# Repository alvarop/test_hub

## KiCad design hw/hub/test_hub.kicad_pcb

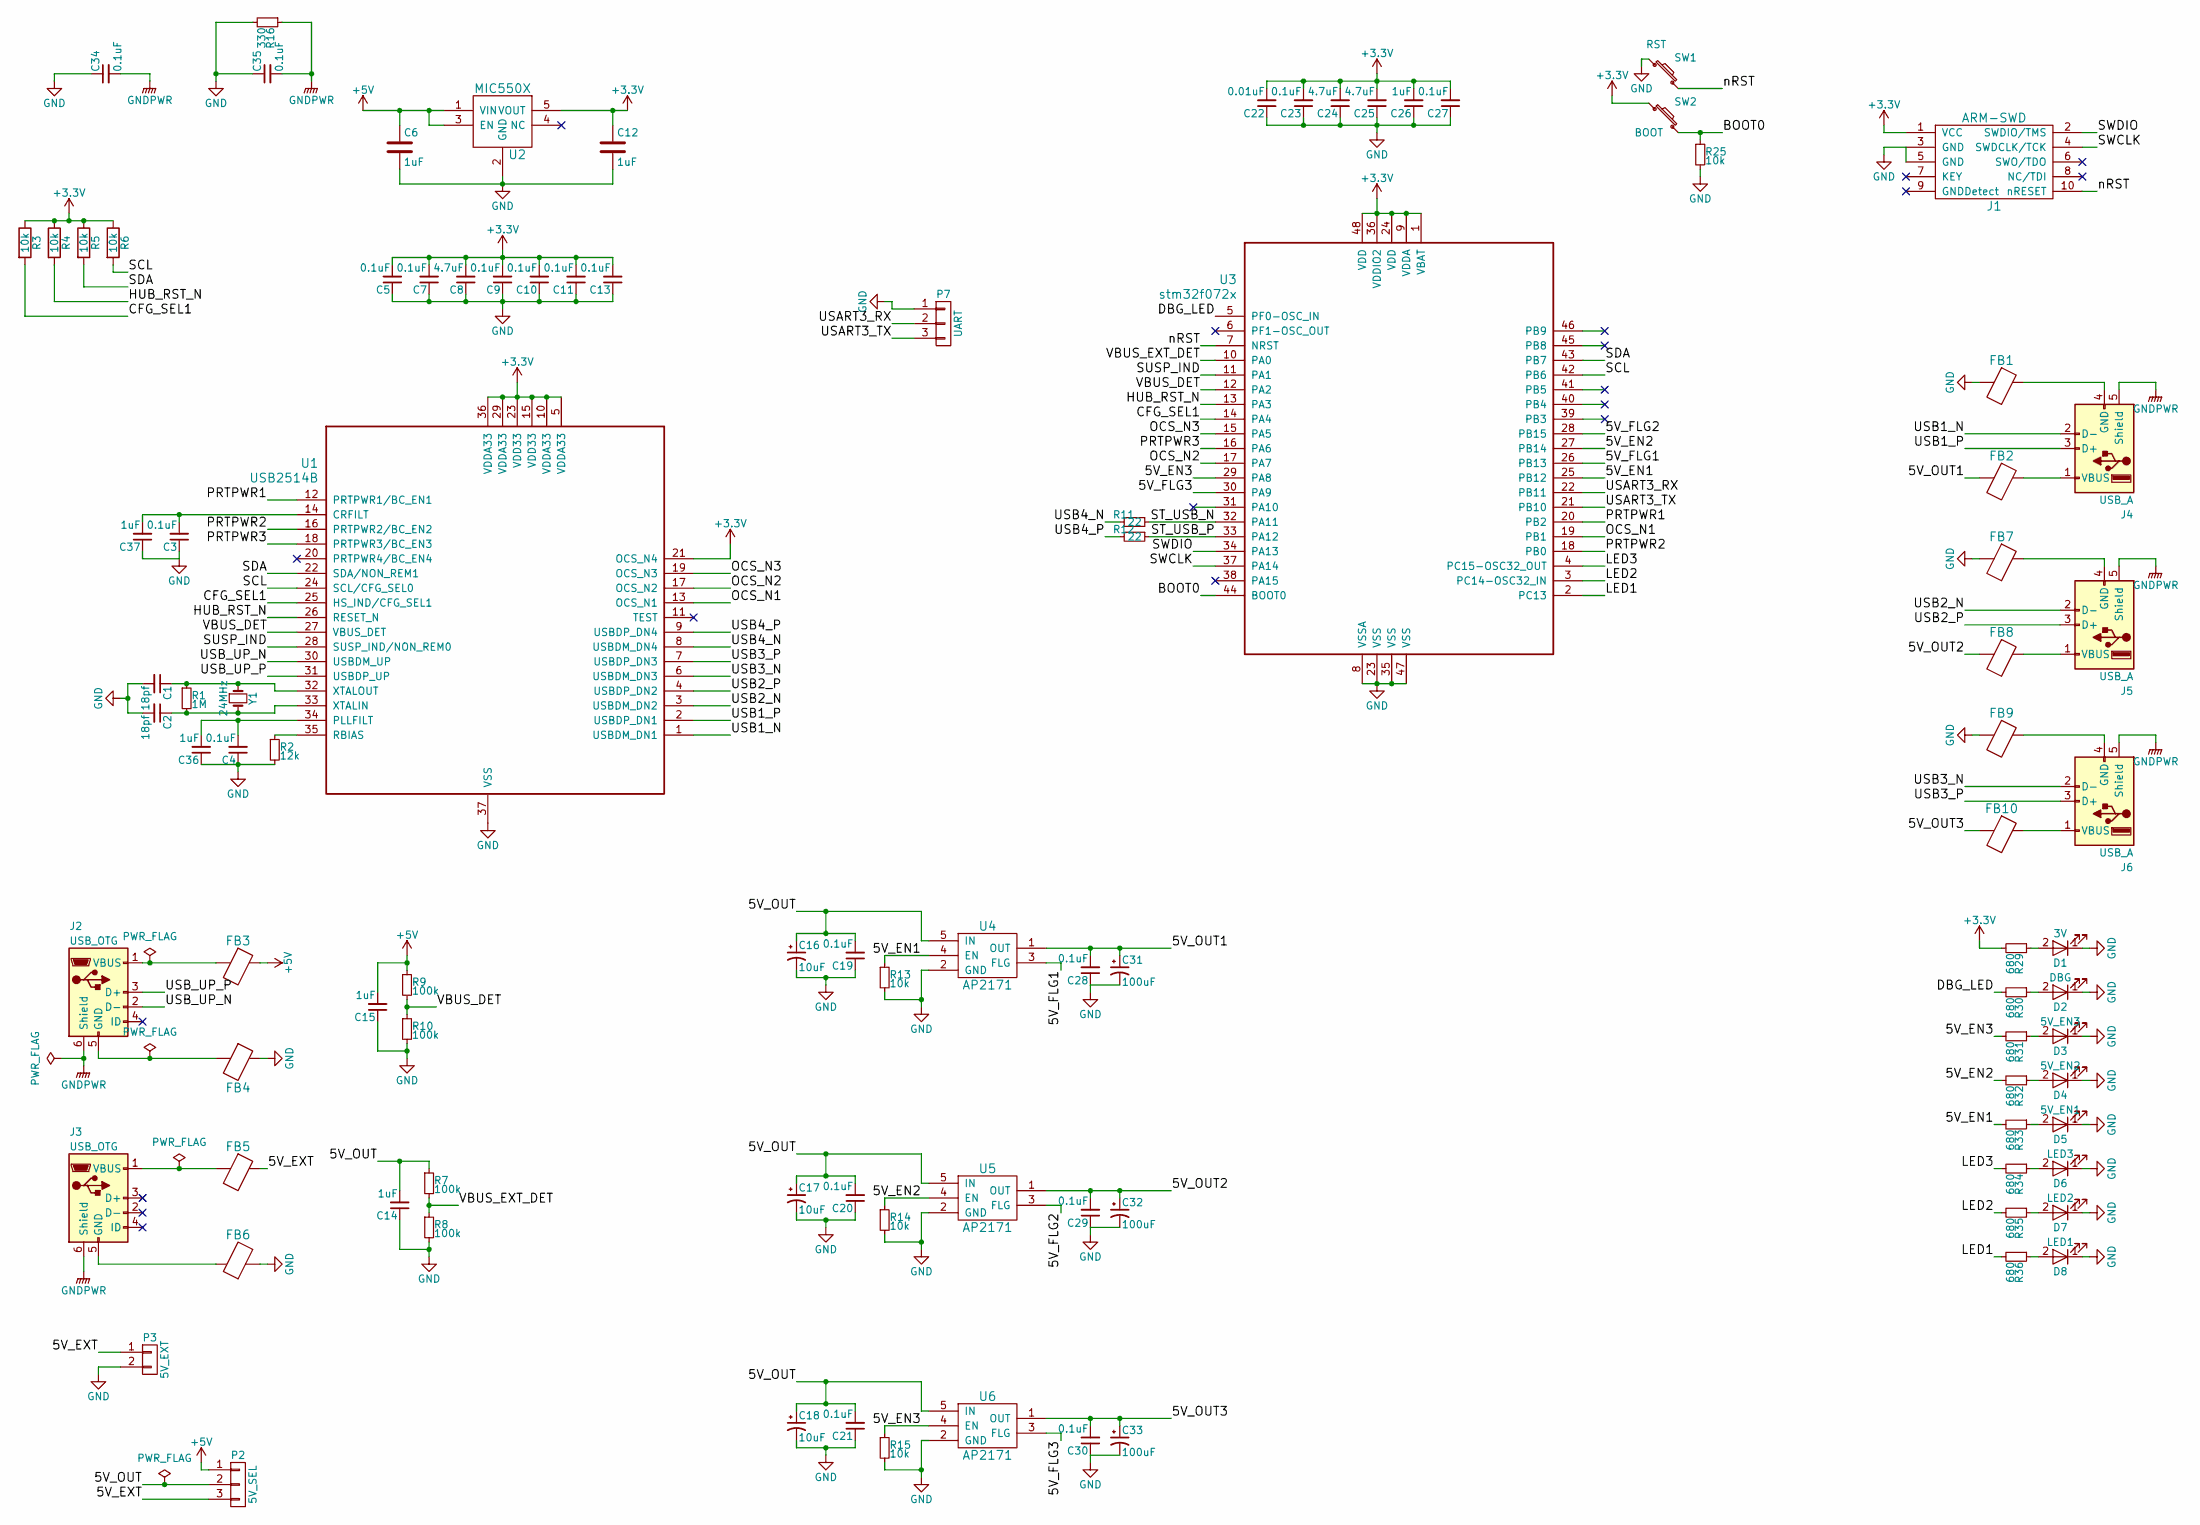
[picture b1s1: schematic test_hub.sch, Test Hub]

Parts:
C1, C2: 18pf; C_0603; MPN CL10C180JB8NNNC
C3, C4, C5, C7, C9, C10, C11, C13, C19, C20, C21, C23, C27, C28, C29, C30, C34, C35: 0.1uF; C_0603; MPN CC0603ZRY5V9BB104
C6, C12, C14, C15, C26, C36, C37: 1uF; C_0603; MPN GRM188R61C105KA93D
C8, C24, C25: 4.7uF; C_0603; MPN CL10B475KQ8NQNC
C16, C17, C18: 10uF; c_elec_4x5.3; MPN UWX1C100MCL1GB
C22: 0.01uF; C_0603; MPN CL21B103KBANNNC
C31, C32, C33: 100uF; c_elec_6.3x5.7; MPN UWR1A101MCL1GB
D1: 3V; LED_0805; MPN LG R971-KN-1
D2: DBG; LED_0805; MPN LG R971-KN-1
D3: 5V_EN3; LED_0805; MPN LG R971-KN-1
D4: 5V_EN2; LED_0805; MPN LG R971-KN-1
D5: 5V_EN1; LED_0805; MPN LG R971-KN-1
D6: LED3; LED_0805; MPN LG R971-KN-1
D7: LED2; LED_0805; MPN LG R971-KN-1
D8: LED1; LED_0805; MPN LG R971-KN-1
FB1, FB2, FB3, FB4, FB5, FB6, FB7, FB8, FB9, FB10: Ferrite_Bead; R_0603; MPN CIS10P221NC
J1: ARM-SWD; ARM_SWD_SMD; MPN 20021121-00010C4LF
J2, J3: USB_OTG; USB_MICRO_B; MPN 629105150521
J4, J5, J6: USB_A; 292303-1; MPN 292303-1
P2: 5V_SEL; Pin_Header_Straight_1x03
P3: 5V_EXT; Pin_Header_Straight_1x02
P7: UART; Pin_Header_Straight_1x03
R1: 1M; R_0603; MPN ERJ-3GEYJ105V
R2: 12k; R_0603; MPN ERJ-3EKF1202V
R3, R4, R5, R6, R13, R14, R15, R25: 10k; R_0603; MPN RC0603FR-0710KL
R7, R8, R9, R10: 100k; R_0603; MPN ERJ-3GEYJ104V
R11, R12: 22; R_0603; MPN RC0603FR-0722RL
R16: 330; R_0603; MPN RC0603JR-07330RL
R29, R30, R31, R32, R33, R34, R35, R36: 680; R_0603; MPN RC0603JR-07680RL
SW1: RST; PTS645SM43SMTR92; MPN PTS645SM43SMTR92
SW2: BOOT; PTS645SM43SMTR92; MPN PTS645SM43SMTR92
U1: USB2514B; SQFN36; MPN USB2514B/M2
U2: MIC550X; SOT-23(M5); MPN MIC5504-3.3YM5-TR
U3: stm32f072x; LQFP48; MPN STM32F072RBT6
U4, U5, U6: AP2171; SOT-25; MPN AP2171WG-7
Y1: 24MHz; HCM49; MPN HCM4924000000ABJT

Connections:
+3V3: C5.2, C7.2, C8.2, C9.2, C10.2, C11.2, C12.1, C13.2, C22.2, C23.2, C24.2, C25.2, C26.2, C27.2, J1.1 (VCC), R3.1, R4.1, R5.1, R6.1, R29.2, SW2.1, U1.5 (VDDA33), U1.10 (VDDA33), U1.15 (VDD33), U1.21 (OCS_N4), U1.23 (VDD33), U1.29 (VDDA33), U1.36 (VDDA33), U2.5 (VOUT), U3.1 (VBAT), U3.9 (VDDA), U3.24 (VDD), U3.36 (VDDIO2), U3.48 (VDD)
+5V: C6.1, C15.2, FB3.2, P2.1, R9.1, U2.1 (VIN), U2.3 (EN)
/5V_EN1: R13.1, R33.2, U3.25 (PB12), U4.4 (EN)
/5V_EN2: R14.1, R32.2, U3.27 (PB14), U5.4 (EN)
/5V_EN3: R15.1, R31.2, U3.29 (PA8), U6.4 (EN)
/5V_EXT: FB5.2, P2.3, P3.1
/5V_FLG1: U3.26 (PB13), U4.3 (FLG)
/5V_FLG2: U3.28 (PB15), U5.3 (FLG)
/5V_FLG3: U3.30 (PA9), U6.3 (FLG)
/5V_OUT: C14.2, C16.1, C17.1, C18.1, C19.2, C20.2, C21.2, P2.2, R7.1, U4.5 (IN), U5.5 (IN), U6.5 (IN)
/5V_OUT1: C28.2, C31.1, FB2.1, U4.1 (OUT)
/5V_OUT2: C29.2, C32.1, FB8.1, U5.1 (OUT)
/5V_OUT3: C30.2, C33.1, FB10.1, U6.1 (OUT)
/BOOT0: R25.1, SW2.2, U3.44 (BOOT0)
/CFG_SEL1: R3.2, U1.25 (HS_IND/CFG_SEL1), U3.14 (PA4)
/DBG_LED: R30.2, U3.5 (PF0-OSC_IN)
/HUB_RST_N: R4.2, U1.26 (RESET_N), U3.13 (PA3)
/LED1: R36.2, U3.2 (PC13)
/LED2: R35.2, U3.3 (PC14-OSC32_IN)
/LED3: R34.2, U3.4 (PC15-OSC32_OUT)
/OCS_N1: U1.13 (OCS_N1), U3.19 (PB1)
/OCS_N2: U1.17 (OCS_N2), U3.17 (PA7)
/OCS_N3: U1.19 (OCS_N3), U3.15 (PA5)
/PRTPWR1: U1.12 (PRTPWR1/BC_EN1), U3.20 (PB2)
/PRTPWR2: U1.16 (PRTPWR2/BC_EN2), U3.18 (PB0)
/PRTPWR3: U1.18 (PRTPWR3/BC_EN3), U3.16 (PA6)
/SCL: R6.2, U1.24 (SCL/CFG_SEL0), U3.42 (PB6)
/SDA: R5.2, U1.22 (SDA/NON_REM1), U3.43 (PB7)
/ST_USB_N: R11.1, U3.32 (PA11)
/ST_USB_P: R12.1, U3.33 (PA12)
/SUSP_IND: U1.28 (SUSP_IND/NON_REM0), U3.11 (PA1)
/SWCLK: J1.4 (SWDCLK/TCK), U3.37 (PA14)
/SWDIO: J1.2 (SWDIO/TMS), U3.34 (PA13)
/USART3_RX: P7.2, U3.22 (PB11)
/USART3_TX: P7.3, U3.21 (PB10)
/USB1_N: J4.2 (D-), U1.1 (USBDM_DN1)
/USB1_P: J4.3 (D+), U1.2 (USBDP_DN1)
/USB2_N: J5.2 (D-), U1.3 (USBDM_DN2)
/USB2_P: J5.3 (D+), U1.4 (USBDP_DN2)
/USB3_N: J6.2 (D-), U1.6 (USBDM_DN3)
/USB3_P: J6.3 (D+), U1.7 (USBDP_DN3)
/USB4_N: R11.2, U1.8 (USBDM_DN4)
/USB4_P: R12.2, U1.9 (USBDP_DN4)
/USB_UP_N: J2.2 (D-), U1.30 (USBDM_UP)
/USB_UP_P: J2.3 (D+), U1.31 (USBDP_UP)
/VBUS_DET: R9.2, R10.1, U1.27 (VBUS_DET), U3.12 (PA2)
/VBUS_EXT_DET: R7.2, R8.1, U3.10 (PA0)
/nRST: J1.10 (nRESET), SW1.2, U3.7 (NRST)
GND: C1.2, C2.2, C3.1, C4.1, C5.1, C6.2, C7.1, C8.1, C9.1, C10.1, C11.1, C12.2, C13.1, C14.1, C15.1, C16.2, C17.2, C18.2, C19.1, C20.1, C21.1, C22.1, C23.1, C24.1, C25.1, C26.1, C27.1, C28.1, C29.1, C30.1, C31.2, C32.2, C33.2, C34.1, C35.1, C36.1, C37.1, D1.1 (K), D2.1 (K), D3.1 (K), D4.1 (K), D5.1 (K), D6.1 (K), D7.1 (K), D8.1 (K), FB1.1, FB4.2, FB6.1, FB7.1, FB9.1, J1.3 (GND), J1.5 (GND), P3.2, P7.1, R2.2, R8.2, R10.2, R13.2, R14.2, R15.2, R16.2, R25.2, SW1.1, U1.37 (VSS), U2.2 (GND), U3.8 (VSSA), U3.23 (VSS), U3.35 (VSS), U3.47 (VSS), U4.2 (GND), U5.2 (GND), U6.2 (GND)
GNDPWR: C34.2, C35.2, J2.6 (Shield), J3.6 (Shield), J4.5 (Shield), J5.5 (Shield), J6.5 (Shield), R16.1
unnamed: C1.1, R1.1, U1.32 (XTALOUT), Y1.1
unnamed: C2.1, R1.2, U1.33 (XTALIN), Y1.2
unnamed: C3.2, C37.2, U1.14 (CRFILT)
unnamed: C4.2, C36.2, U1.34 (PLLFILT)
unnamed: D1.2 (A), R29.1
unnamed: D2.2 (A), R30.1
unnamed: D3.2 (A), R31.1
unnamed: D4.2 (A), R32.1
unnamed: D5.2 (A), R33.1
unnamed: D6.2 (A), R34.1
unnamed: D7.2 (A), R35.1
unnamed: D8.2 (A), R36.1
unnamed: FB1.2, J4.4 (GND)
unnamed: FB2.2, J4.1 (VBUS)
unnamed: FB3.1, J2.1 (VBUS)
unnamed: FB4.1, J2.5 (GND)
unnamed: FB5.1, J3.1 (VBUS)
unnamed: FB6.2, J3.5 (GND)
unnamed: FB7.2, J5.4 (GND)
unnamed: FB8.2, J5.1 (VBUS)
unnamed: FB9.2, J6.4 (GND)
unnamed: FB10.2, J6.1 (VBUS)
unnamed: R2.1, U1.35 (RBIAS)

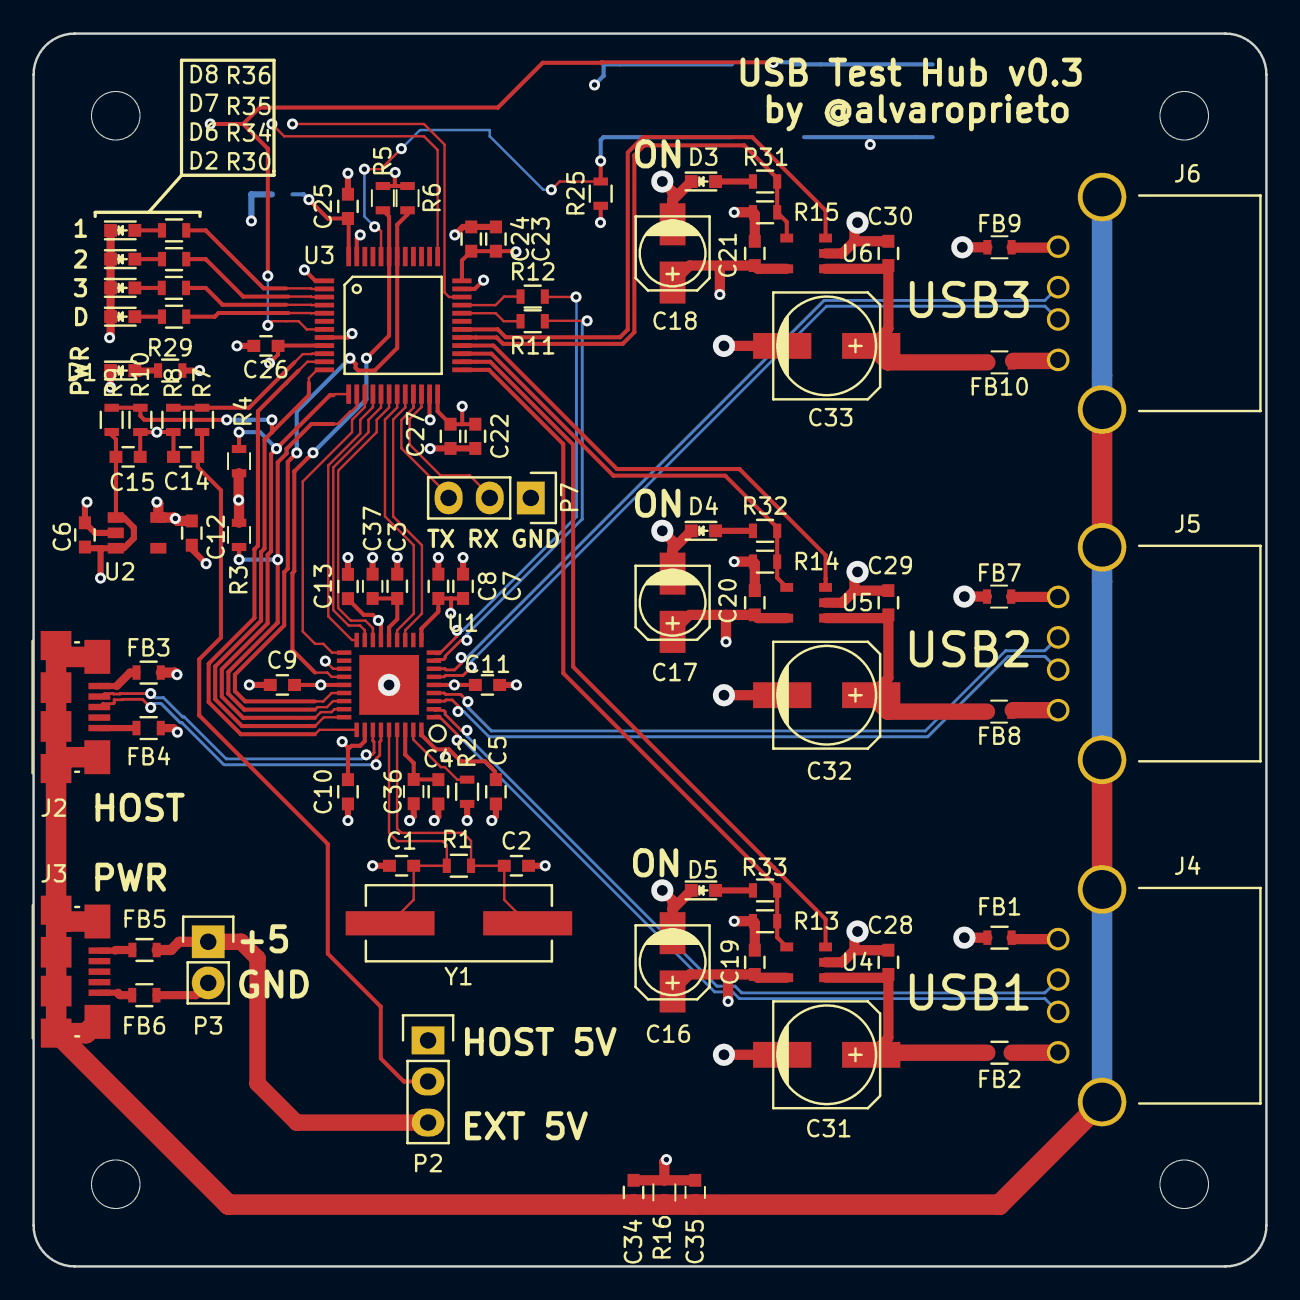
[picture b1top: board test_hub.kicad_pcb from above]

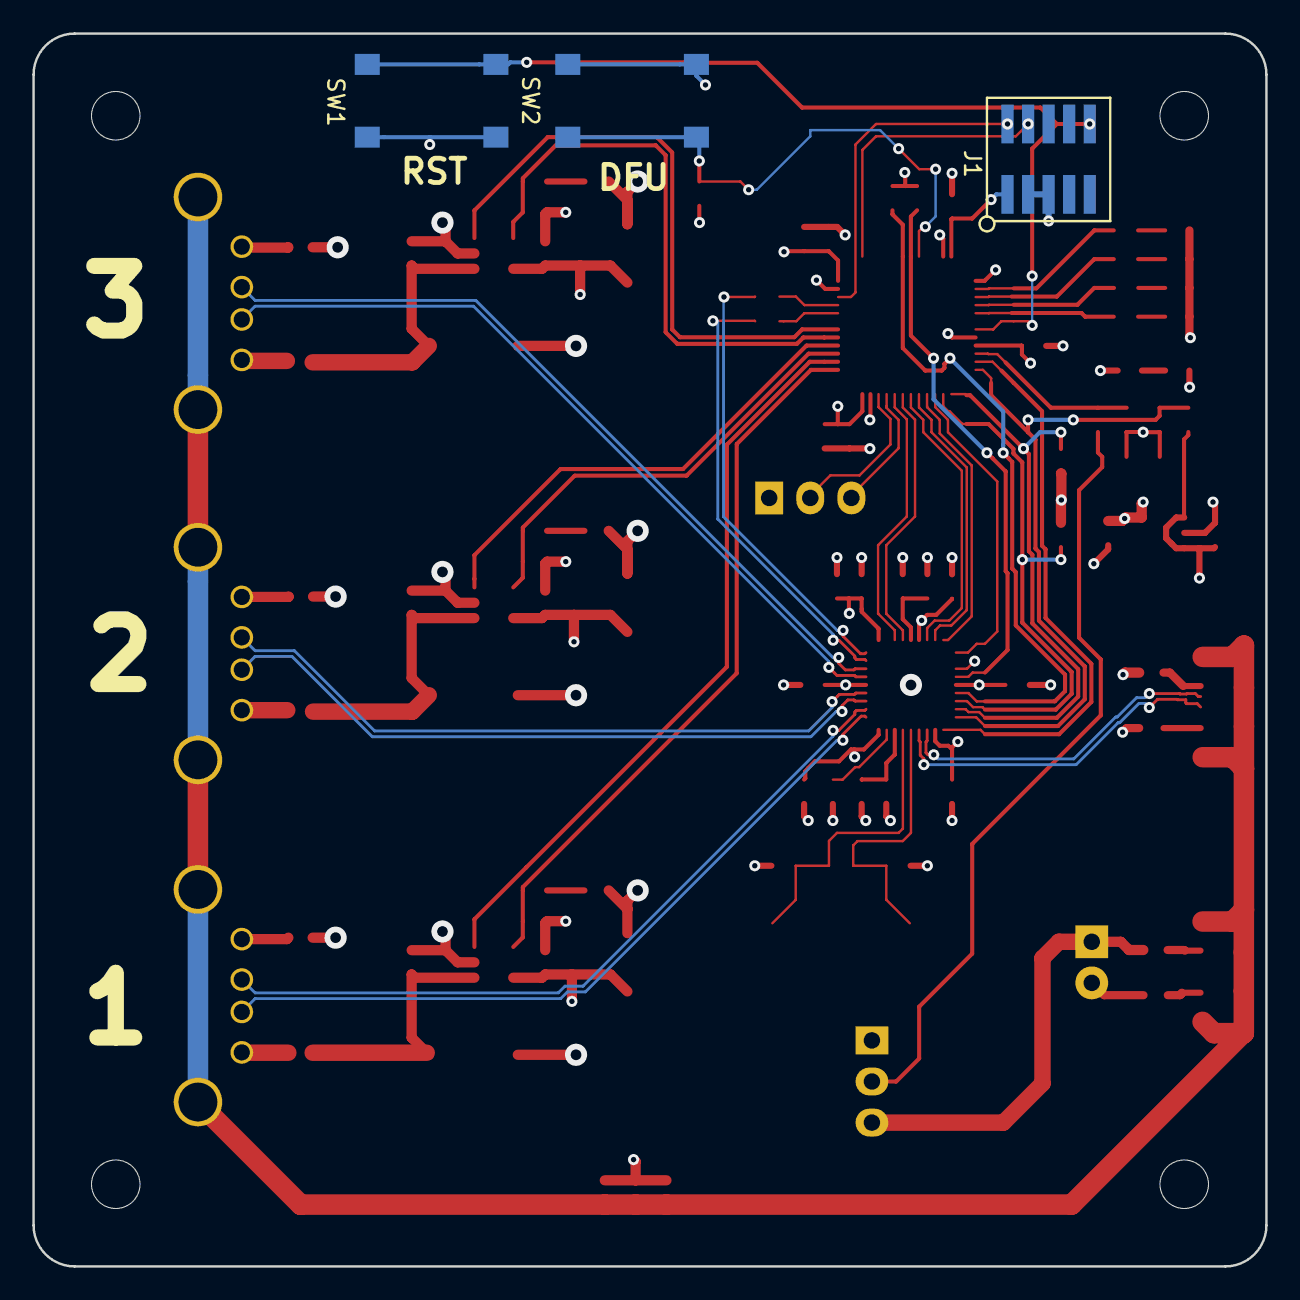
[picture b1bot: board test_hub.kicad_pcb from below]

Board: 4 copper layers, 76.2 x 76.2 mm, 98 parts (3 on the bottom side), 73 nets.

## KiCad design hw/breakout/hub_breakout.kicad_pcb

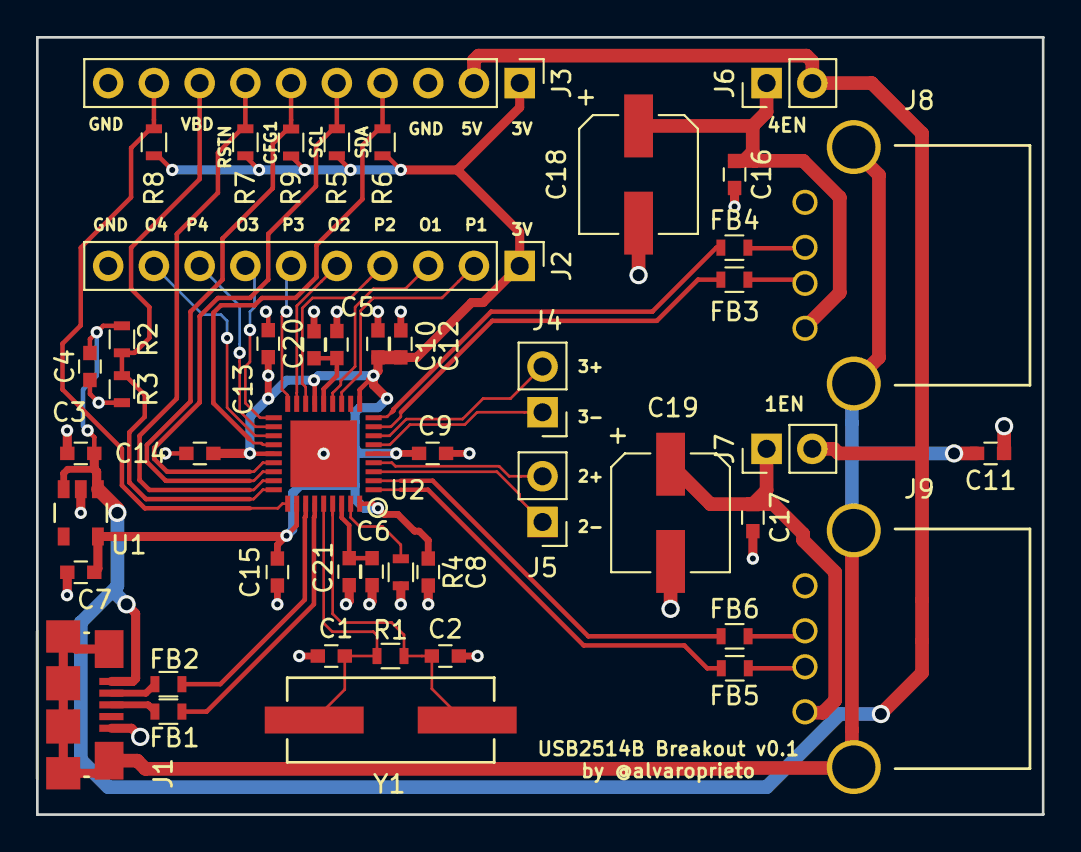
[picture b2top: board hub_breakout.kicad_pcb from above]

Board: 2 copper layers, 55.9 x 43.2 mm, 48 parts (0 on the bottom side), 41 nets.

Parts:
C1, C2: 18pF; C_0603
C3, C4, C7, C20, C21: 1uF; C_0603
C5, C6, C8, C9, C11, C12, C13, C14, C15, C16, C17: 0.1uF; C_0603
C10: 4.7uF; C_0603
C18, C19: 100uF; CP_Elec_6.3x5.7
FB1, FB2, FB3, FB4, FB5, FB6: Ferrite; R_0603
J1: USB_OTG; USB_MICRO_B
J2, J3: CONN_01X10; Pin_Header_Straight_1x10_Pitch2.54mm
J4, J5, J6, J7: CONN_01X02; Pin_Header_Straight_1x02_Pitch2.54mm
J8, J9: USB_A; 292303-1
R1: 1M; R_0603
R2, R3: 100k; R_0603
R4: 12k; R_0603
R5, R6, R7, R8, R9: 10k; R_0603
U1: MIC550X; SOT-23(M5)
U2: USB2514B; SQFN36
Y1: 24MHz; HCM49

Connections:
+3V3: C7.1, C8.1, C9.1, C10.1, C12.1, C13.1, C14.1, C15.1, J2.1, J3.1, R5.1, R6.1, R7.1, R8.1, R9.1, U1.5, U2.5, U2.10, U2.15, U2.23, U2.29, U2.36
+5V: C3.1, C4.1, J1.1, J3.2, J6.2, J7.2, R2.1, U1.1, U1.3
/CFG_SEL1: J3.6, R9.2, U2.25
/OCS_N1: J2.3, U2.13
/OCS_N2: J2.5, U2.17
/OCS_N3: J2.7, U2.19
/OCS_N4: J2.9, U2.21
/PRTPWR1: J2.2, U2.12
/PRTPWR2: J2.4, U2.16
/PRTPWR3: J2.6, U2.18
/PRTPWR4: J2.8, U2.20
/RESET_N: J3.7, R7.2, U2.26
/SCL: J3.5, R5.2, U2.24
/SDA: J3.4, R6.2, U2.22
/SUSP_IND: J3.9, R8.2, U2.28
/USB1_N: FB5.2, U2.1
/USB1_P: FB6.2, U2.2
/USB2_N: J5.1, U2.3
/USB2_P: J5.2, U2.4
/USB3_N: J4.1, U2.6
/USB3_P: J4.2, U2.7
/USB4_N: FB3.2, U2.8
/USB4_P: FB4.2, U2.9
/USB_UP_N: FB2.1, U2.30
/USB_UP_P: FB1.1, U2.31
/VBUS_DET: J3.8, R2.2, R3.1, U2.27
GND: C1.2, C2.2, C3.2, C4.2, C5.2, C6.2, C7.2, C8.2, C9.2, C10.2, C11.1, C12.2, C13.2, C14.2, C15.2, C16.2, C17.2, C18.2, C19.2, C20.2, C21.2, J1.5, J2.10, J3.3, J3.10, J8.4, J9.4, R3.2, R4.2, U1.2, U2.37
GNDPWR: C11.2, J1.6, J8.5, J9.5
unnamed: C1.1, R1.1, U2.32, Y1.1
unnamed: C2.1, R1.2, U2.33, Y1.2
unnamed: C16.1, C18.1, J6.1, J8.1
unnamed: C17.1, C19.1, J7.1, J9.1
unnamed: C5.1, C20.1, U2.14
unnamed: C6.1, C21.1, U2.34
unnamed: FB1.2, J1.3
unnamed: FB2.2, J1.2
unnamed: FB3.1, J8.2
unnamed: FB4.1, J8.3
unnamed: FB5.1, J9.2
unnamed: FB6.1, J9.3
unnamed: R4.1, U2.35

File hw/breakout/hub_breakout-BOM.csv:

Title,
Revision,
Date,
Generated,Mon 27 Mar 2017 06:29:56 PM PDT
Company,
Comment 1,
Comment 2,
Comment 3,
Comment 4,
Total Parts,48
Total Unique Parts,17



Ref,Qty,Value,Footprint,MPN,
C3 C7 C4 C20 C21 ,5,1uF,Capacitors_SMD:C_0603,GRM188R61C105KA93D
C1 C2 ,2,18pF,Capacitors_SMD:C_0603,CL10C180JB8NNNC
C8 C9 C12 C13 C14 C15 C11 C5 C6 C17 C16 ,11,0.1uF,Capacitors_SMD:C_0603,CC0603ZRY5V9BB104
C10 ,1,4.7uF,Capacitors_SMD:C_0603,CL10B475KQ8NQNC
C19 C18 ,2,100uF,Capacitors_SMD:CP_Elec_6.3x5.7,UWR1A101MCL1GB
FB2 FB1 FB5 FB6 FB3 FB4 ,6,Ferrite,Resistors_SMD:R_0603,BLM18EG221SN1D
J1 ,1,USB_OTG,alvarop:USB_MICRO_B,10118193-0001LF
J2 J3 ,2,CONN_01X10,Pin_Headers:Pin_Header_Straight_1x10_Pitch2.54mm, 
J8 J9 ,2,USB_A,footprints:292303-1,292303-1
J6 J7 J4 J5 ,4,CONN_01X02,Pin_Headers:Pin_Header_Straight_1x02_Pitch2.54mm, 
R1 ,1,1M,Resistors_SMD:R_0603,ERJ-3GEYJ105V
R4 ,1,12k,Resistors_SMD:R_0603,ERJ-3EKF1202V
R2 R3 ,2,100k,Resistors_SMD:R_0603,ERJ-3GEYJ104V
R7 R6 R5 R9 R8 ,5,10k,Resistors_SMD:R_0603,RC0603FR-0710KL
U2 ,1,USB2514B,footprints:SQFN36,USB2514B/M2
U1 ,1,MIC550X,footprints:SOT-23(M5),MIC5504-3.3YM5-TR
Y1 ,1,24MHz,footprints:HCM49,HCM4924000000ABJT




BOM made with KICAD_BOM_WIZARD (https://github.com/HashDefineElectronics/KiCad_BOM_Wizard.git)
Generated Mon 27 Mar 2017 06:29:56 PM PDT

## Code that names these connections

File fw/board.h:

#ifndef __PINS_H__
#define __PINS_H__

#define _LED1_PORT GPIOC
#define _LED1_PIN 13

#define _LED2_PORT GPIOC
#define _LED2_PIN 14

#define _LED3_PORT GPIOC
#define _LED3_PIN 15

#define _DBG_LED_PORT GPIOF
#define _DBG_LED_PIN 0

#define _VBUS_EXT_DET_PORT GPIOA
#define _VBUS_EXT_DET_PIN 1

#define _SUSP_IND_PORT GPIOB
#define _SUSP_IND_PIN 3

#define _VBUS_DET_PORT GPIOA
#define _VBUS_DET_PIN 0

#define _HUB_RST_N_PORT GPIOB
#define _HUB_RST_N_PIN 15

#define _CFG_SEL1_PORT GPIOB
#define _CFG_SEL1_PIN 4

#define _OCS_N3_PORT GPIOA
#define _OCS_N3_PIN 5

#define _PRTPWR3_PORT GPIOA
#define _PRTPWR3_PIN 6

#define _OCS_N2_PORT GPIOA
#define _OCS_N2_PIN 7

#define _PRTPWR2_PORT GPIOB
#define _PRTPWR2_PIN 0

#define _OCS_N1_PORT GPIOB
#define _OCS_N1_PIN 1

#define _PRTPWR1_PORT GPIOB
#define _PRTPWR1_PIN 2

#define _USART3_TX_PORT GPIOB
#define _USART3_TX_PIN 10

#define _USART3_RX_PORT GPIOB
#define _USART3_RX_PIN 11

#define _5V_EN1_PORT GPIOB
#define _5V_EN1_PIN 12

#define _5V_FLG1_PORT GPIOA
#define _5V_FLG1_PIN 8

#define _5V_EN2_PORT GPIOB
#define _5V_EN2_PIN 13

#define _5V_FLG2_PORT GPIOA
#define _5V_FLG2_PIN 9

#define _5V_EN3_PORT GPIOB
#define _5V_EN3_PIN 14

#define _5V_FLG3_PORT GPIOA
#define _5V_FLG3_PIN 10

#define _ST_USB_N_PORT GPIOA
#define _ST_USB_N_PIN 11

#define _ST_USB_P_PORT GPIOA
#define _ST_USB_P_PIN 12

#define _SWDIO_PORT GPIOA
#define _SWDIO_PIN 13

#define _SWCLK_PORT GPIOA
#define _SWCLK_PIN 14

#define _SCL_PORT GPIOB
#define _SCL_PIN 6

#define _SDA_PORT GPIOB
#define _SDA_PIN 7

#define _SNS1_PORT GPIOA
#define _SNS1_PIN 2

#define _SNS2_PORT GPIOA
#define _SNS2_PIN 3

#define _SNS3_PORT GPIOA
#define _SNS3_PIN 4

#endif  // __PINS_H__

// #ifndef __PINS_H__
// #define __PINS_H__

// #define _LED1_PORT GPIOC
// #define _LED1_PIN 13

// #define _LED2_PORT GPIOC
// #define _LED2_PIN 14

// #define _LED3_PORT GPIOC
// #define _LED3_PIN 15

// #define _DBG_LED_PORT GPIOF
// #define _DBG_LED_PIN 0

// #define _VBUS_EXT_DET_PORT GPIOA
// #define _VBUS_EXT_DET_PIN 0

// #define _SUSP_IND_PORT GPIOA
// #define _SUSP_IND_PIN 1

// #define _VBUS_DET_PORT GPIOA
// #define _VBUS_DET_PIN 2

// #define _HUB_RST_N_PORT GPIOA
// #define _HUB_RST_N_PIN 3

// #define _CFG_SEL1_PORT GPIOA
// #define _CFG_SEL1_PIN 4

// #define _OCS_N3_PORT GPIOA
// #define _OCS_N3_PIN 5

// #define _PRTPWR3_PORT GPIOA
// #define _PRTPWR3_PIN 6

// #define _OCS_N2_PORT GPIOA
// #define _OCS_N2_PIN 7

// #define _PRTPWR2_PORT GPIOB
// #define _PRTPWR2_PIN 0

// #define _OCS_N1_PORT GPIOB
// #define _OCS_N1_PIN 1

// #define _PRTPWR1_PORT GPIOB
// #define _PRTPWR1_PIN 2

// #define _USART3_TX_PORT GPIOB
// #define _USART3_TX_PIN 10

// #define _USART3_RX_PORT GPIOB
// #define _USART3_RX_PIN 11

// #define _5V_EN1_PORT GPIOB
// #define _5V_EN1_PIN 12

// #define _5V_FLG1_PORT GPIOB
// #define _5V_FLG1_PIN 13

// #define _5V_EN2_PORT GPIOB
// #define _5V_EN2_PIN 14

// #define _5V_FLG2_PORT GPIOB
// #define _5V_FLG2_PIN 15

// #define _5V_EN3_PORT GPIOA
// #define _5V_EN3_PIN 8

// #define _5V_FLG3_PORT GPIOA
// #define _5V_FLG3_PIN 9

// #define _ST_USB_N_PORT GPIOA
// #define _ST_USB_N_PIN 11

// #define _ST_USB_P_PORT GPIOA
// #define _ST_USB_P_PIN 12

// #define _SWDIO_PORT GPIOA
// #define _SWDIO_PIN 13

// #define _SWCLK_PORT GPIOA
// #define _SWCLK_PIN 14

// #define _SCL_PORT GPIOB
// #define _SCL_PIN 6

// #define _SDA_PORT GPIOB
// #define _SDA_PIN 7

// #endif  // __PINS_H__

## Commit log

2017-02-11 adding .gitignore
2017-02-11 Starting work on test_hub schematic
2017-02-11 First draft of schematic
2017-02-12 Schematic and footprint assignments done
2017-02-12 Start working on PCB...
2017-02-12 Fixed schematic bugs and added SWD/UART
2017-02-13 PCB routing done (I think)
2017-02-14 Forgot to connect some things...
2017-02-14 Updated MPN's
2017-02-15 Minor changes after exporting gerbers
2017-02-19 Kicad version update changes
2017-02-19 Adding label for ST usb wires
2017-02-21 Adding initial firmware image for test_hub
2017-03-16 Added board file (first test with new board!)
2017-03-16 Port power enable/disable working!
2017-03-21 Moving test_hub files under hub/ directory
2017-03-22 Adding usb2514b breakout
    Because I can't get test_hub working...
2017-03-28 Adding BOM for breakout
2017-04-22 Fixing unconnected pads....
    Not sure how I missed so many unconnected things :(
    MAKE SURE YOU CLICK ON "LIST UNCONNECTED" AFTER RUNNING DRC!!!!!!!!!!!
2017-04-22 Hub is now working!!!!!!!!!!!!!!!!!
    Configured over i2c :D :D :D
2017-04-22 Splitting functions into separate files
2017-05-10 Move hub files to hw directory
2017-05-10 Split into hub and sense_hub
2017-05-10 Begin removing sense resistors from hub
2017-05-10 Breakout should also be in hw directory
2017-05-13 Update test_hub
    No more rescued components
    Ripped up all traces
    Starting layout again
2017-05-14 More test_hub work
2017-05-19 Continued routing work on test_hub
2017-05-25 Almost done with test_hub layout
2017-05-25 All connections made!
    Now I just need to fix the USB clearances...
2017-05-25 Layout done!
2017-05-26 Cleaned up silkscreen
2017-06-11 Now working with test hub v0.2 with uart
2017-06-16 Serial terminal ove rUSB finally working :D :D :D :D
    Can't print before USB is initialized of course...
    Printing to stderr doesn't seem to be entirely working though :(
2017-08-20 Fixed stderr printing!
    Apparently _write() needs to return a valid value... who knew!
2017-09-14 Fixing usb cdc code that was eating bytes
2017-09-14 Get rid of old ADC stuff
2017-09-14 Trying to get more consistent looking code
    Applied `clang-format -style=Google <filename>` to the files I created
2017-09-16 Adding DFU support in FW :D
2018-01-09 Testing 4 layer PCB!
    Released v0.3 to JLPCB
2018-05-28 Adding hub config generator
2018-05-28 Adding old adc files
2020-04-18 Committing old changes
